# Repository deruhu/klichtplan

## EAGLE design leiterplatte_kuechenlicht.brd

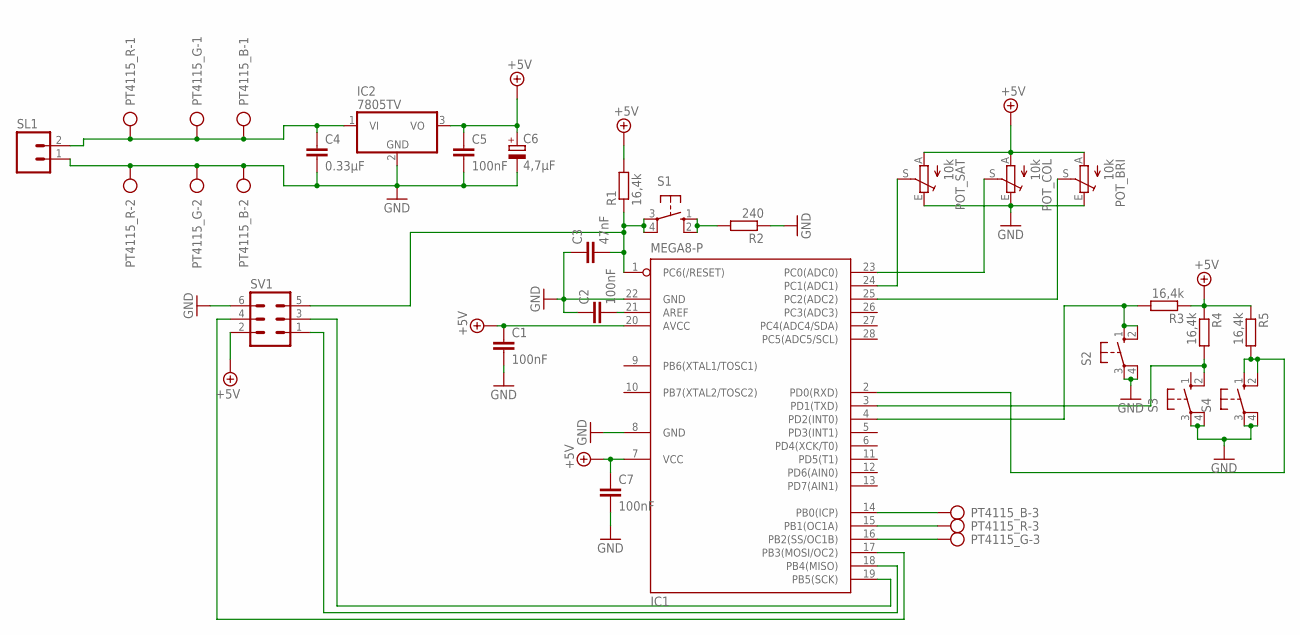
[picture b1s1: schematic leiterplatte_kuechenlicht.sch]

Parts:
C1, C2, C5, C7: 100nF; C2.5-3
C3: 47nF; C050-025X075
C4: 0.33µF; C2.5-3
C6: 4,7µF; E2,5-6E
IC1: MEGA8-P; DIL28-3
IC2: 7805TV; TO220V
POT_BRI: 10k; CIP20C-6MM
POT_COL: 10k; CIP20C-6MM
POT_SAT: 10k; CIP20C-6MM
PT4115_B, PT4115_G, PT4115_R: AK300/3
R1, R3, R4, R5: 16,4k; 0204/7
R2: 240; 0204/7
S1, S2, S3, S4: 10-XX; B3F-10XX
SL1: M02; 02P
SV1: ML6

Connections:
+5V: C1.1, C5.1, C6.+, C7.1, IC1.7 (VCC), IC1.20 (AVCC), IC2.3 (VO), POT_BRI.A, POT_COL.A, POT_SAT.A, R1.2, R3.1, R4.1, R5.1, SV1.2
GND: C1.2, C2.1, C3.1, C4.2, C5.2, C6.-, C7.2, IC1.8 (GND), IC1.22 (GND), IC2.2 (GND), POT_BRI.E, POT_COL.E, POT_SAT.E, PT4115_B.2, PT4115_G.2, PT4115_R.2, R2.1, S2.3, S2.4 (P1), S3.3, S3.4 (P1), S4.3, S4.4 (P1), SL1.1, SV1.6
unnamed: R2.2, S1.1 (S), S1.2 (S1)
unnamed: C4.1, IC2.1 (VI), PT4115_B.1, PT4115_G.1, PT4115_R.1, SL1.2
unnamed: C2.2, IC1.21 (AREF)
unnamed: IC1.24 (PC1(ADC1)), POT_SAT.S
unnamed: IC1.23 (PC0(ADC0)), POT_COL.S
unnamed: IC1.25 (PC2(ADC2)), POT_BRI.S
unnamed: IC1.15 (PB1(OC1A)), PT4115_R.3
unnamed: C3.2, IC1.1 (PC6(/RESET)), R1.1, S1.3, S1.4 (P1), SV1.5
unnamed: IC1.19 (PB5(SCK)), SV1.3
unnamed: IC1.18 (PB4(MISO)), SV1.1
unnamed: IC1.17 (PB3(MOSI/OC2)), SV1.4
unnamed: IC1.16 (PB2(SS/OC1B)), PT4115_G.3
unnamed: IC1.14 (PB0(ICP)), PT4115_B.3
unnamed: IC1.2 (PD0(RXD)), R5.2, S4.1 (S), S4.2 (S1)
unnamed: IC1.3 (PD1(TXD)), R4.2, S3.2 (S1)
unnamed: IC1.4 (PD2(INT0)), R3.2, S2.1 (S), S2.2 (S1)

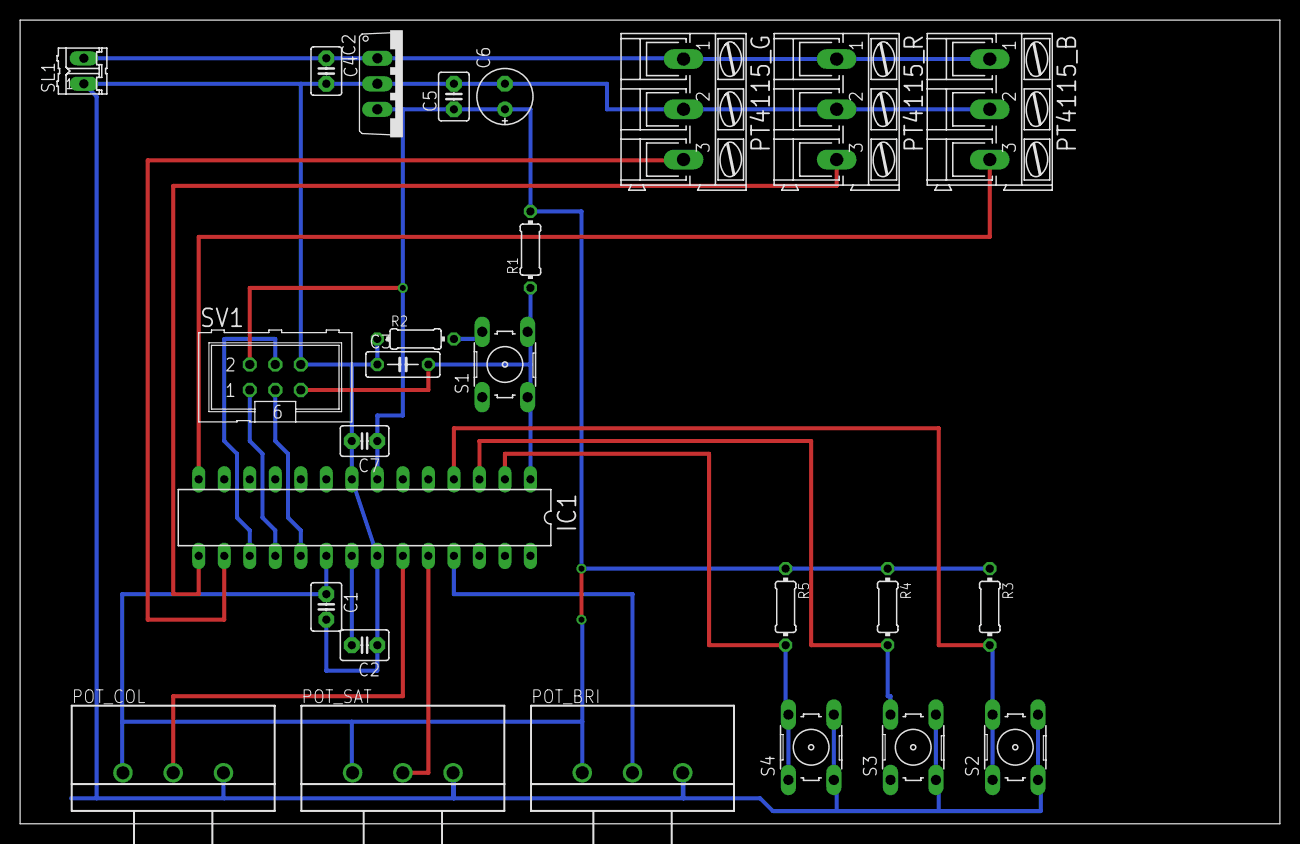
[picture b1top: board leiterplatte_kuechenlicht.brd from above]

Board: 2 copper layers, 125.4 x 80.0 mm, 26 parts (0 on the bottom side), 18 nets.

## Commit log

2013-02-17 start
